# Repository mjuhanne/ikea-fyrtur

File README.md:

# ikea-fyrtur

## Introduction

This is a ESP8266 WiFi module PCB to be used with Ikea Fyrtur or Kadrilj roller blinds. It substitutes the original Ikea Trådfri (Zigbee) based board.

#### Enhancements:
 - Easier and more stable connectivity with non-Ikea home automation systems (such as Home Assistant) without additional hardware hub (please see [esp-fyrtur repository](https://github.com/mjuhanne/fyrtur-esp) for the software)
 - Designed to be powered with wired 5-7.5V DC power adapter, so no more charging the battery every few months! (5V charger can be used only when a custom fyrtur motor firmware is used. For this, see [fyrtur-motor-board repository](https://github.com/mjuhanne/fyrtur-motor-board))
 - On-board 1A fuse for extra safety
 - Additional connection header allows the use of other platforms (such as ESP32 or Arduino) since now the battery compartment is empty and can hold larger wireless modules
 - Optional I2C Temperature and humidity sensor (Si7021 or HTU21D)
 - Optional Neopixel RGB-led to be used as a status LED

## Assembly
 
Ready Gerber and BOM/component position files for PCB production and SMT assembly for JLCPCB.com
 - The tiny motor connector PCB should be desoldered from the original board and re-used.
 - The only self-sourced components are the ESP12F module, temperature sensor and fuse (The buttons and LED can be ordered or alternatively scavenged from the original board)

## Programming

Programming can be done via the 2mm pitch UART header using FTDI adapter. Alternatively a special [TagConnect](https://www.tag-connect.com/product/tc2030-nl-ftdi-ttl-232r-usb-to-tc2030-no-legs-serial-cable) adapter can be used if you don't want to solder the UART header (not tested yet).

## Interface board

 The PCB can also be used as a plain interface board (with buttons and LED populated, with optional temperature sensor). In this case only the following components are needed:
 
#### Connector header:
  - J1 EXT_CTRL (1x7, 2mm pitch) (or solder female Dupont wires directly to the header)

#### Buttons and debounce circuitry:
 - Panasonic right angle tactile switches (EVQ-P7L01P)
 - R11,R12 (10K)
 - R9 (120R), R10 (10K)
 - C6, C7 (100nF)

#### LED:
 - any 3.5mm diameter LED
 - R13 (270R - 1K, depending on the LED forward voltage drop and desired brightness)

#### Temperature sensor components:
 - U3 (SI7021 / HTU21D)
 - R6, R4 (10k)
 - C5 (100nF)
 - J6 I2C header (1x4, 2mm pitch) (or solder female Dupont wires directly to the header)

### Example wiring for ESP32 (DevKitC V4)
  - J1:1 <--> GND
  - J1:2 <--> 3V3
  - J1:3 <--> D21 (BTN_UP)
  - J1:4 <--> D5 (Motor UART RX)
  - J1:5 <--> D23 (Motor UART TX)
  - J1:6 <--> D22 (BTN_DOWN)
  - J1:7 <--> D18 (LED)
 
#### Optional I2C temperature sensor:
  - J6:3 <--> D19 (SCL)
  - J6:4 <--> D13 (SDA)

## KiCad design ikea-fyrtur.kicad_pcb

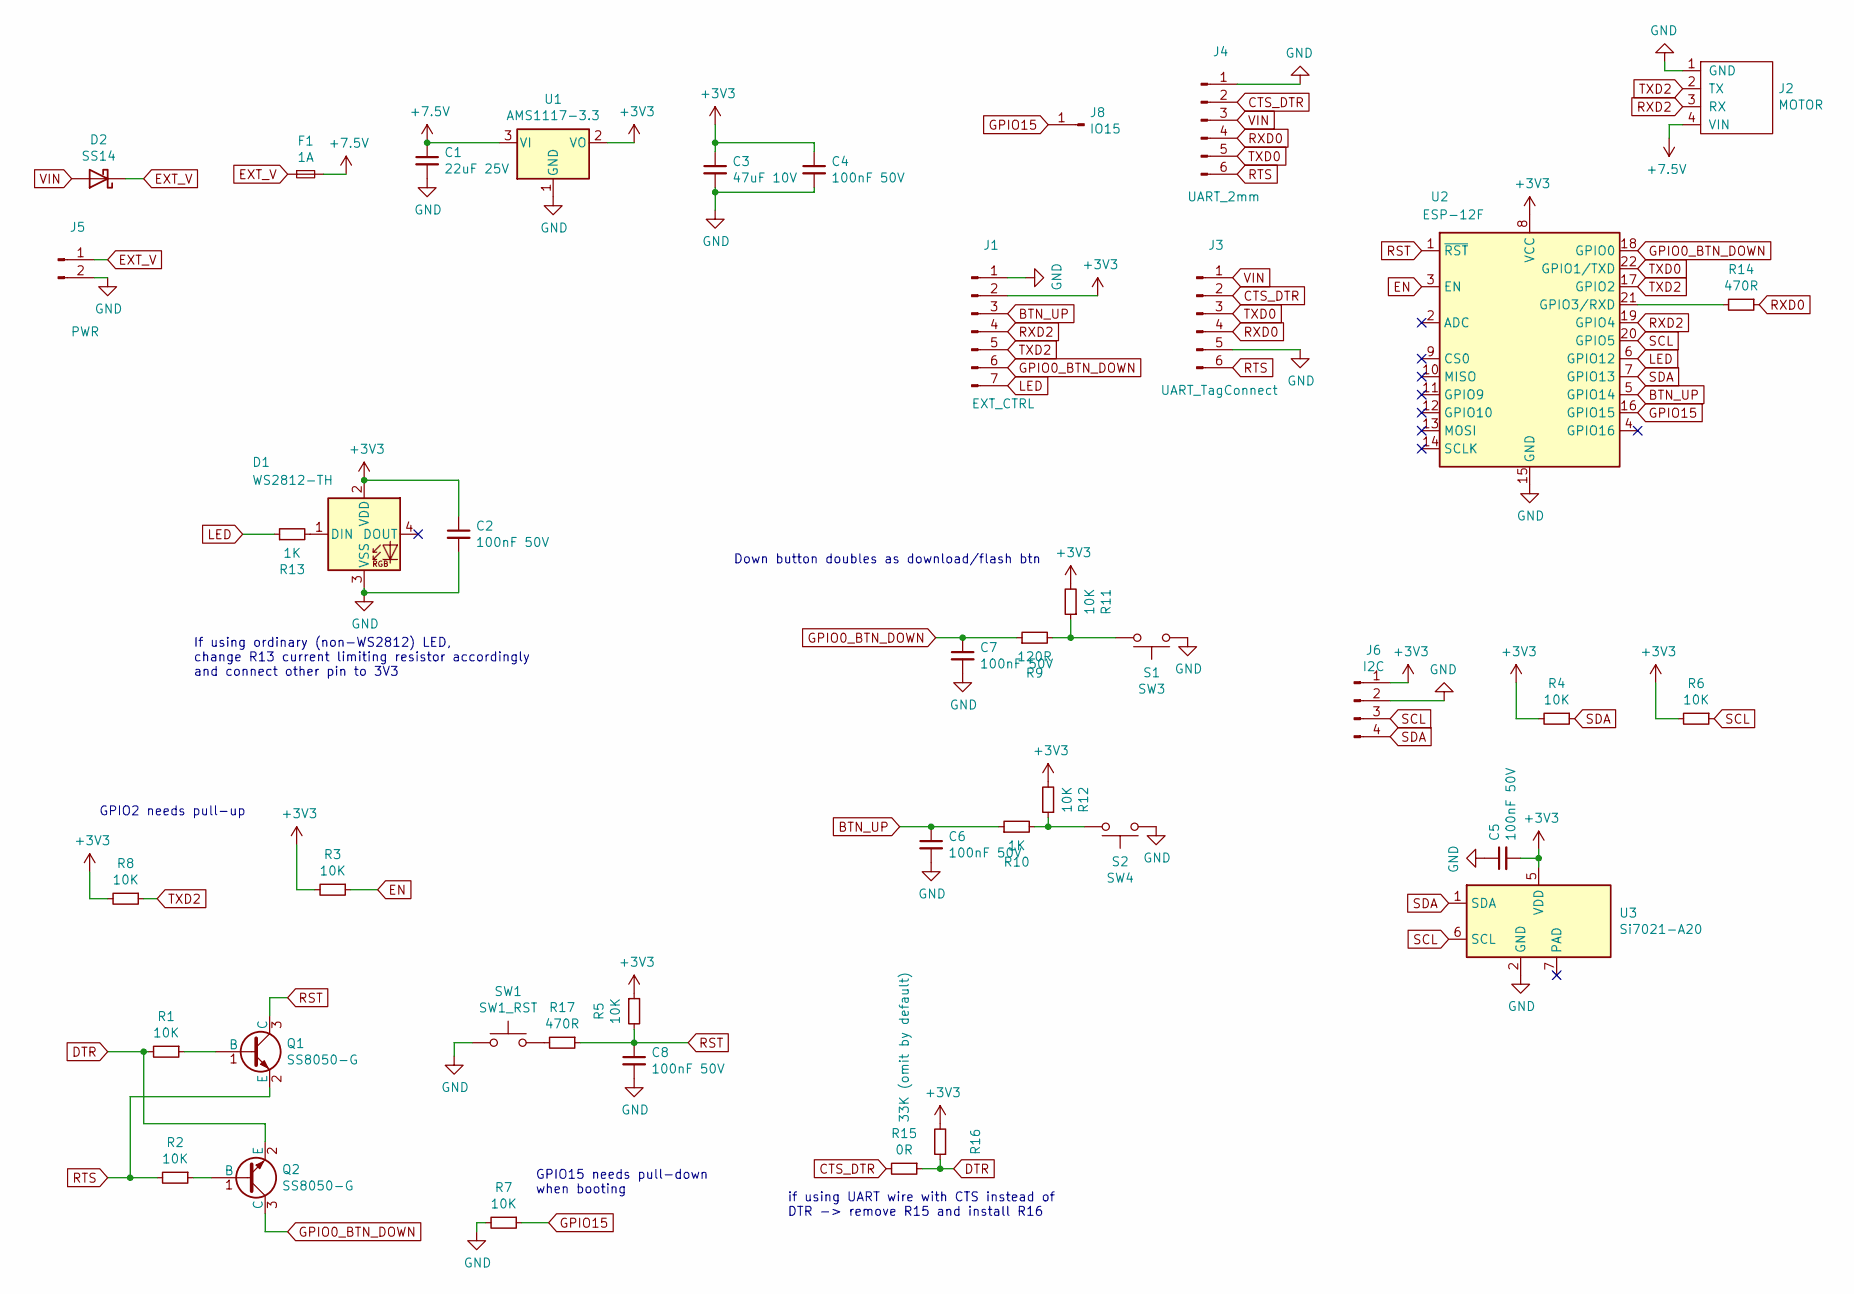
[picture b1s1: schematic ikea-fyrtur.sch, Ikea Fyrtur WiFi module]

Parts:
C1: 22uF 25V; C_0805_2012Metric_Pad1.15x1.40mm_HandSolder; LCSC Part C45783
C2, C4, C5, C6, C7, C8: 100nF 50V; C_0603_1608Metric_Pad1.05x0.95mm_HandSolder; LCSC Part C14663
C3: 47uF 10V; C_1206_3216Metric_Pad1.42x1.75mm_HandSolder; LCSC Part C96123
D1: WS2812-TH; JLCPCB BOM 0
D2: SS14; D_SMA; LCSC Part C2480
F1: 1A; Fuse_0805_2012Metric_Pad1.15x1.40mm_HandSolder; JLCPCB BOM 0
J1: EXT_CTRL; PinHeader_1x07_P2.00mm_Vertical; JLCPCB BOM 0
J2: MOTOR; Fyrtyr-Motor-Connector; JLCPCB BOM 0
J3: UART_TagConnect; Tag-Connect_TC2030-IDC-NL_2x03_P1.27mm_Vertical; JLCPCB BOM 0
J4: UART_2mm; PinHeader_1x06_P2.00mm_Vertical; JLCPCB BOM 0
J5: PWR; PinHeader_1x02_P2.00mm_Vertical; JLCPCB BOM 0
J6: I2C; PinHeader_1x04_P2.00mm_Vertical; JLCPCB BOM 0
J8: IO15; PinHeader_1x01_P2.00mm_Vertical; JLCPCB BOM 0
Q1, Q2: SS8050-G; SOT-23; LCSC Part C2150
R1, R2, R3, R4, R5, R6, R7, R8, R11, R12: 10K; R_0603_1608Metric; LCSC Part C25804
R9: 120R; R_0603_1608Metric; LCSC Part C21190
R10, R13: 1K; R_0603_1608Metric; LCSC Part C21190
R14, R17: 470R; R_0603_1608Metric; LCSC Part C23179
R15: 0R; R_0603_1608Metric; LCSC Part C21189
R16: 33K (omit by default); R_0603_1608Metric; JLCPCB BOM 0
SW1: SW1_RST; SW_SPST_EVQP0; JLCPCB BOM 0
SW3: S1; Panasonic_EVQ-P7L; JLCPCB BOM 0
SW4: S2; Panasonic_EVQ-P7L; JLCPCB BOM 0
U1: AMS1117-3.3; SOT-223-3_TabPin2; LCSC Part C6186
U2: ESP-12F; ESP-12E; JLCPCB BOM 0
U3: Si7021-A20; DFN-6-1EP_3x3mm_P1mm_EP1.5x2.4mm-HS; JLCPCB BOM 0

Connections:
+3V3: C2.1, C3.1, C4.1, C5.2, D1.2 (VDD), J1.2, J6.1, R3.2, R4.2, R5.1, R6.2, R8.2, R11.2, R12.2, R16.2, U1.2 (VO), U2.8 (VCC), U3.5 (VDD)
+7.5V: C1.1, F1.2, J2.4 (VIN), U1.3 (VI)
BTN_UP: C6.1, J1.3, R10.1, U2.5 (GPIO14)
CTS_DTR: J3.2, J4.2, R15.2
DTR: Q2.2 (E), R1.2, R15.1, R16.1
EN: R3.1, U2.3 (EN)
EXT_V: D2.1 (K), F1.1, J5.1
GND: C1.2, C2.2, C3.2, C4.2, C5.1, C6.2, C7.2, C8.2, D1.3 (VSS), J1.1, J2.1 (GND), J3.5, J4.1, J5.2, J6.2, R7.2, SW1.1, SW3.1, SW4.1, U1.1 (GND), U2.15 (GND), U3.2 (GND)
GPIO0_BTN_DOWN: C7.1, J1.6, Q2.3 (C), R9.1, U2.18 (GPIO0)
GPIO15: J8.1, R7.1, U2.16 (GPIO15)
LED: J1.7, R13.1, U2.6 (GPIO12)
unnamed: D1.1 (DIN), R13.2
unnamed: Q1.1 (B), R1.1
unnamed: Q2.1 (B), R2.1
unnamed: R10.2, R12.1, SW4.2
unnamed: R9.2, R11.1, SW3.2
unnamed: R14.2, U2.21 (GPIO3/RXD)
unnamed: R17.2, SW1.2
RST: C8.1, Q1.3 (C), R5.2, R17.1, U2.1 (~RST)
RTS: J3.6, J4.6, Q1.2 (E), R2.2
RXD0: J3.4, J4.4, R14.1
RXD2: J1.4, J2.3 (RX), U2.19 (GPIO4)
SCL: J6.3, R6.1, U2.20 (GPIO5), U3.6 (SCL)
SDA: J6.4, R4.1, U2.7 (GPIO13), U3.1 (SDA)
TXD0: J3.3, J4.5, U2.22 (GPIO1/TXD)
TXD2: J1.5, J2.2 (TX), R8.1, U2.17 (GPIO2)
VIN: D2.2 (A), J3.1, J4.3

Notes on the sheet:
Down button doubles as download/flash btn
if using UART wire with CTS instead of DTR -> remove R15 and install R16
GPIO2 needs pull-up
GPIO15 needs pull-down when booting
If using ordinary (non-WS2812) LED, change R13 current limiting resistor accordingly and connect other pin to 3V3

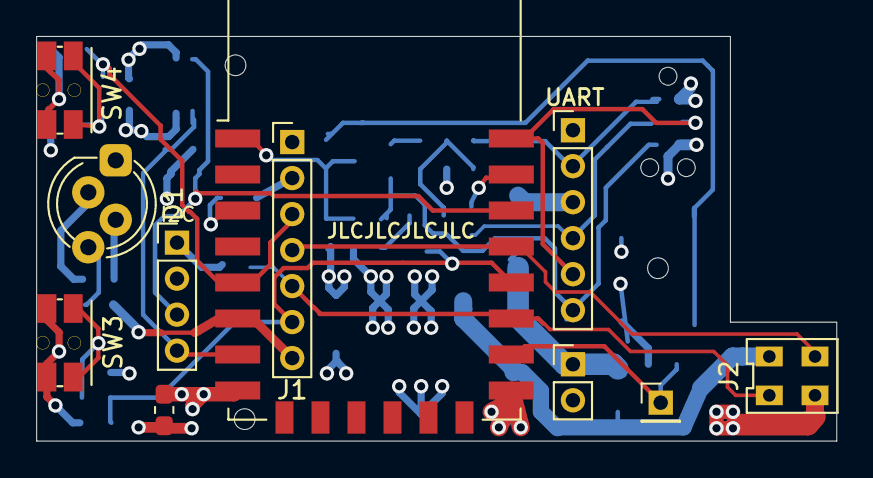
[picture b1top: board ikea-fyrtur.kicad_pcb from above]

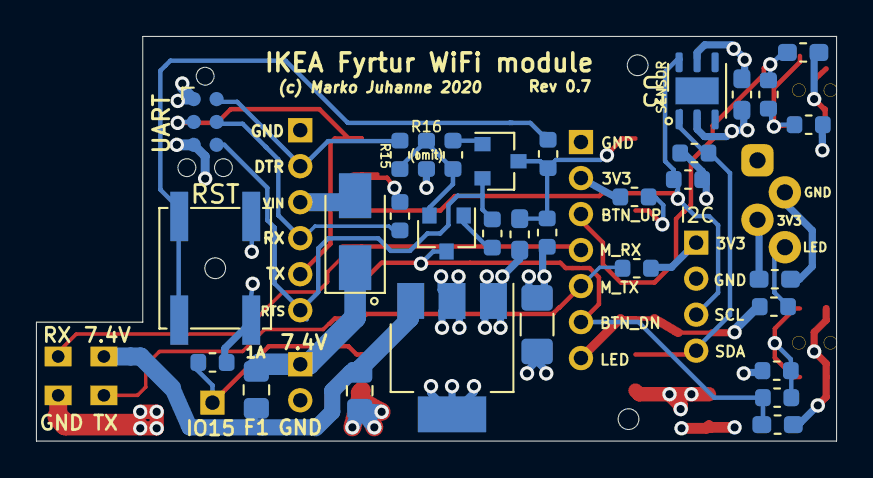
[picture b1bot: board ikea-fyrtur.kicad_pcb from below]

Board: 4 copper layers, 44.5 x 22.5 mm, 43 parts (32 on the bottom side), 27 nets.

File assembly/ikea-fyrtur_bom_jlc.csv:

"Comment","Designator","Footprint","LCSC Part #"
"22uF 25V","C1","C_0805_2012Metric_Pad1.15x1.40mm_HandSolder","C45783"
"47uF 10V","C3","C_1206_3216Metric_Pad1.42x1.75mm_HandSolder","C96123"
"100nF 50V","C4,C7,C6,C2,C5,C8","C_0603_1608Metric_Pad1.05x0.95mm_HandSolder","C14663"
"SS14","D2","D_SMA","C2480"
"SS8050-G","Q1,Q2","SOT-23","C2150"
"10K","R1,R2,R3,R5,R7,R4,R11,R12,R6,R8","R_0603_1608Metric","C25804"
"1K","R10,R13","R_0603_1608Metric","C21190"
"120R","R9","R_0603_1608Metric","C22787"
"470R","R14,R17","R_0603_1608Metric","C23179"
"0R","R15","R_0603_1608Metric","C21189"
"AMS1117-3.3","U1","SOT-223-3_TabPin2","C6186"

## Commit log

2020-10-08 Create LICENSE
2020-10-08 Cache lib, .dcm, .gitignore
2020-11-10 - Change R9 from 1K to 120R (Setting GPIO0 line low via Down-Button may not lower voltage enough otherwise) - Added images, updated README - Change schematic revision to 0.71 (Resistor value change d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
2020-11-10 Add schematic PDF and update README
